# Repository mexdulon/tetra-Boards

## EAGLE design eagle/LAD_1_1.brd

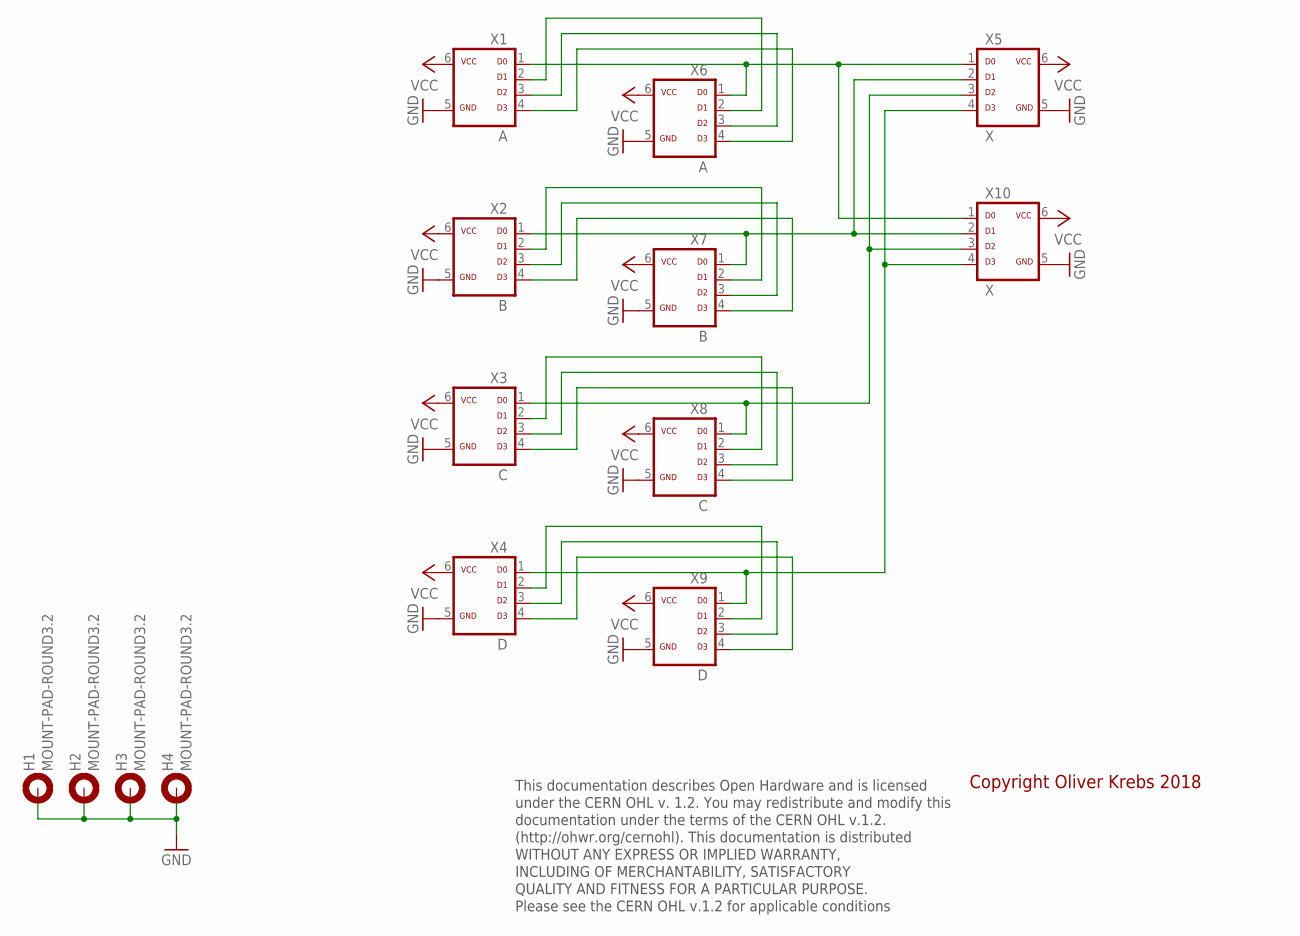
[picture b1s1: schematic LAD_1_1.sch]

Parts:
H1, H2, H3, H4: MOUNT-PAD-ROUND3.2; 3,2-PAD
X1, X6: A; ML-6
X2, X7: B; ML-6
X3, X8: C; ML-6
X4, X9: D; ML-6
X5, X10: X; ML-6

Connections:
GND: H1.B3,2, H2.B3,2, H3.B3,2, H4.B3,2, X1.5, X2.5, X3.5, X4.5, X5.5, X6.5, X7.5, X8.5, X9.5, X10.5
unnamed: X1.2, X6.2
unnamed: X1.3, X6.3
unnamed: X1.4, X6.4
unnamed: X4.1, X5.4, X9.1, X10.4
unnamed: X2.4, X7.4
unnamed: X3.1, X5.3, X8.1, X10.3
unnamed: X2.1, X5.2, X7.1, X10.2
unnamed: X1.1, X5.1, X6.1, X10.1
unnamed: X2.3, X7.3
unnamed: X2.2, X7.2
unnamed: X3.2, X8.2
unnamed: X3.3, X8.3
unnamed: X3.4, X8.4
unnamed: X4.2, X9.2
unnamed: X4.3, X9.3
unnamed: X4.4, X9.4
VCC: X1.6, X2.6, X3.6, X4.6, X5.6, X6.6, X7.6, X8.6, X9.6, X10.6

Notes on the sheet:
This documentation describes Open Hardware and is licensed under the CERN OHL v. 1.2. You may redistribute and modify this documentation under the terms of the CERN OHL v.1.2. (http://ohwr.org/cernohl). This documentation is distributed WITHOUT ANY EXPRESS OR IMPLIED WARRANTY, INCLUDING OF MERCHANT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
Copyright Oliver Krebs 2018

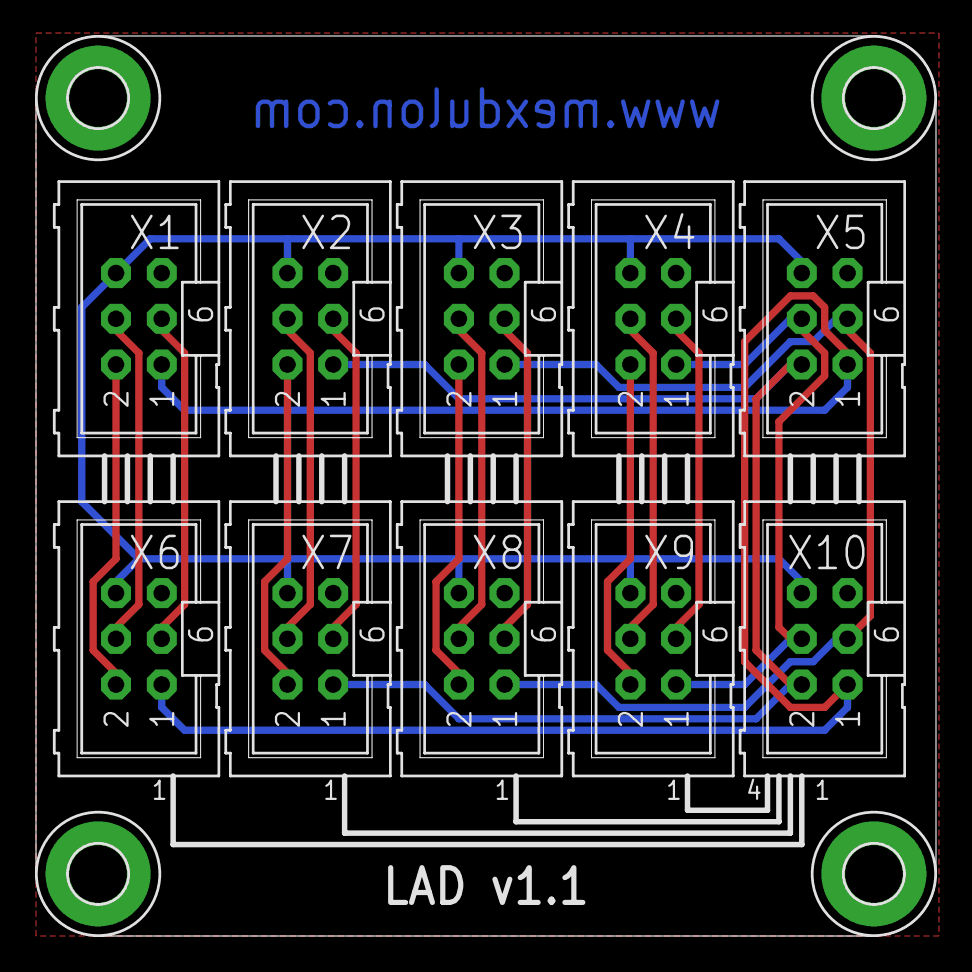
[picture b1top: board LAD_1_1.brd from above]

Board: 2 copper layers, 50.0 x 50.0 mm, 14 parts (0 on the bottom side), 18 nets.

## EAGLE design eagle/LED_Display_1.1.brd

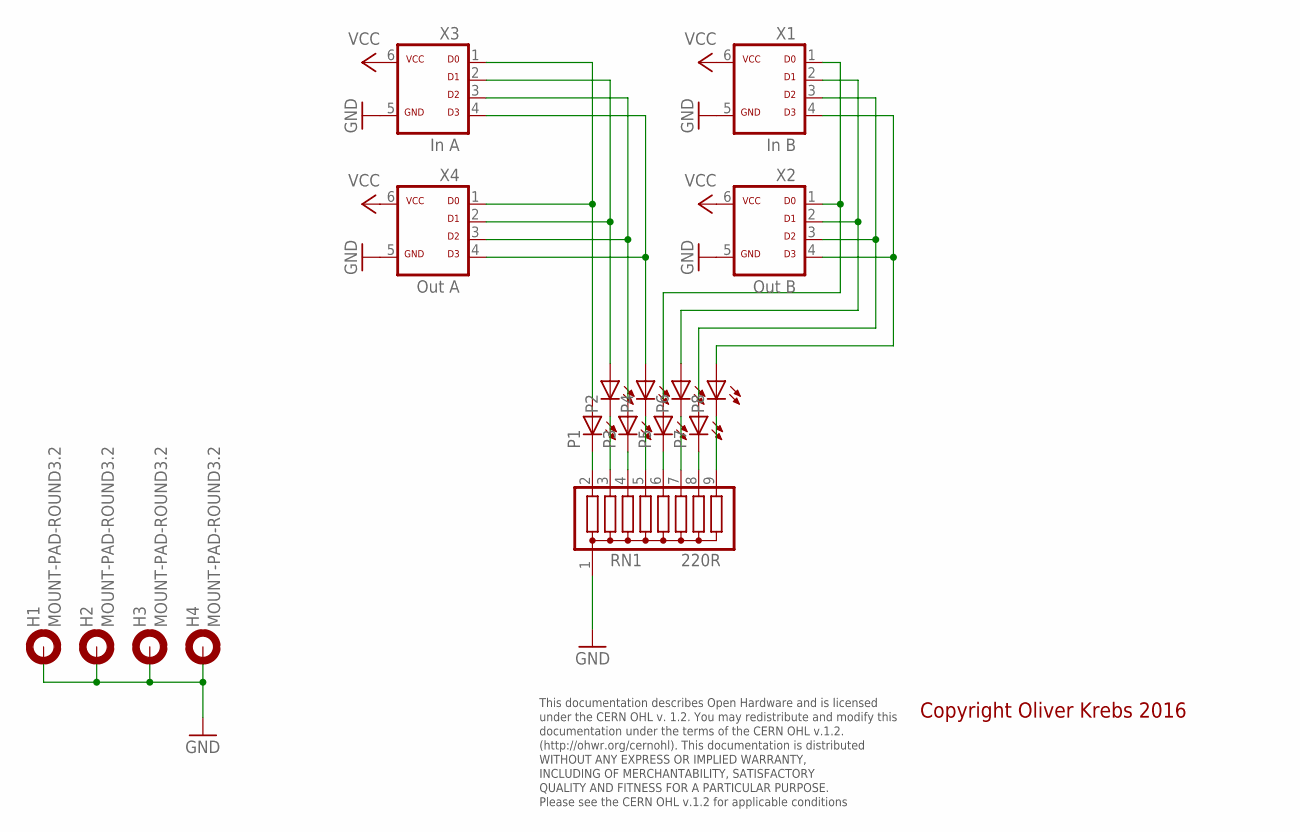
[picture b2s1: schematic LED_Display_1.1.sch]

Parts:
H1, H2, H3, H4: MOUNT-PAD-ROUND3.2; 3,2-PAD
P1, P2, P3, P4, P5, P6, P7, P8: LED3MM
RN1: 220R; SIL9
X1: In B; ML-6
X2: Out B; ML-6
X3: In A; ML-6
X4: Out A; ML-6

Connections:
GND: H1.B3,2, H2.B3,2, H3.B3,2, H4.B3,2, RN1.1, X1.5, X2.5, X3.5, X4.5
unnamed: P5.A, X1.1, X2.1
unnamed: P6.A, X1.2, X2.2
unnamed: P1.A, X3.1, X4.1
unnamed: P8.A, X1.4, X2.4
unnamed: P5.K (C), RN1.6
unnamed: P7.A, X1.3, X2.3
unnamed: P2.A, X3.2, X4.2
unnamed: P4.A, X3.4, X4.4
unnamed: P3.A, X3.3, X4.3
unnamed: P6.K (C), RN1.7
unnamed: P7.K (C), RN1.8
unnamed: P4.K (C), RN1.5
unnamed: P3.K (C), RN1.4
unnamed: P2.K (C), RN1.3
unnamed: P1.K (C), RN1.2
P6: P8.K (C), RN1.9
VCC: X1.6, X2.6, X3.6, X4.6

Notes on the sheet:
This documentation describes Open Hardware and is licensed under the CERN OHL v. 1.2. You may redistribute and modify this documentation under the terms of the CERN OHL v.1.2. (http://ohwr.org/cernohl). This documentation is distributed WITHOUT ANY EXPRESS OR IMPLIED WARRANTY, INCLUDING OF MERCHANT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
Copyright Oliver Krebs 2016

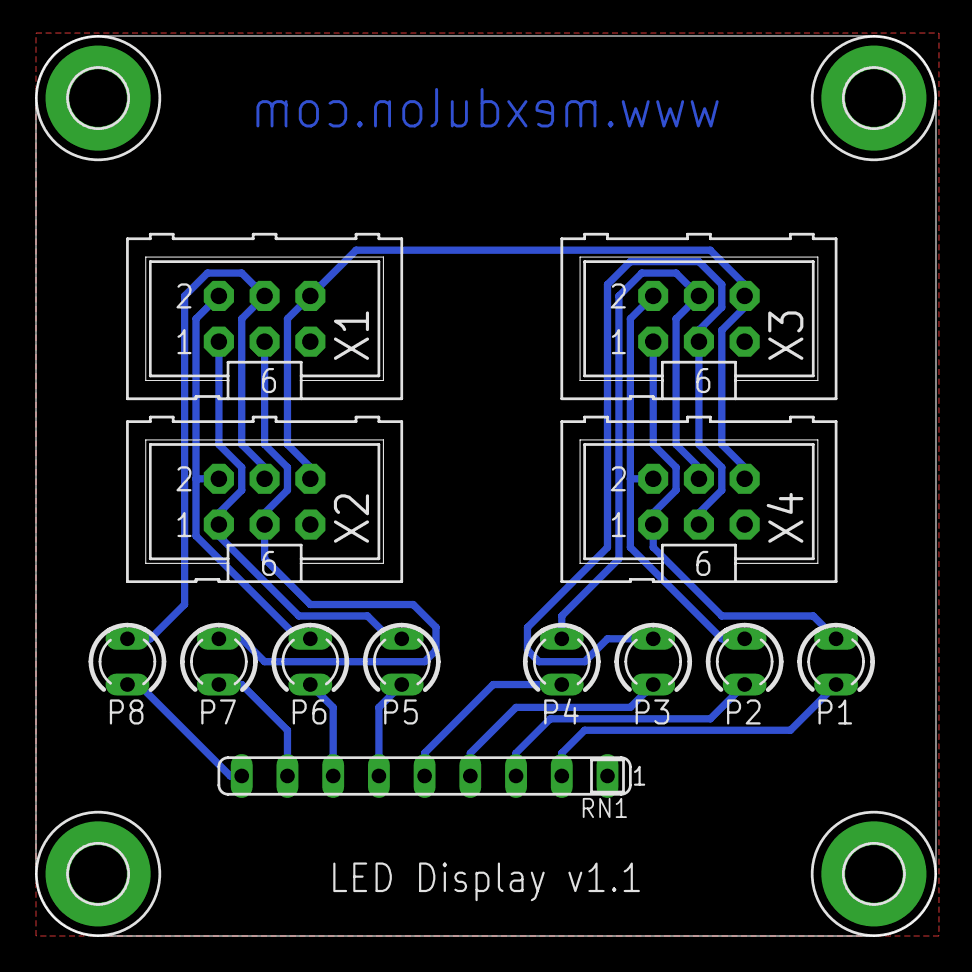
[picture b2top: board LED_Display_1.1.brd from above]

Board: 2 copper layers, 50.0 x 50.0 mm, 17 parts (0 on the bottom side), 18 nets.

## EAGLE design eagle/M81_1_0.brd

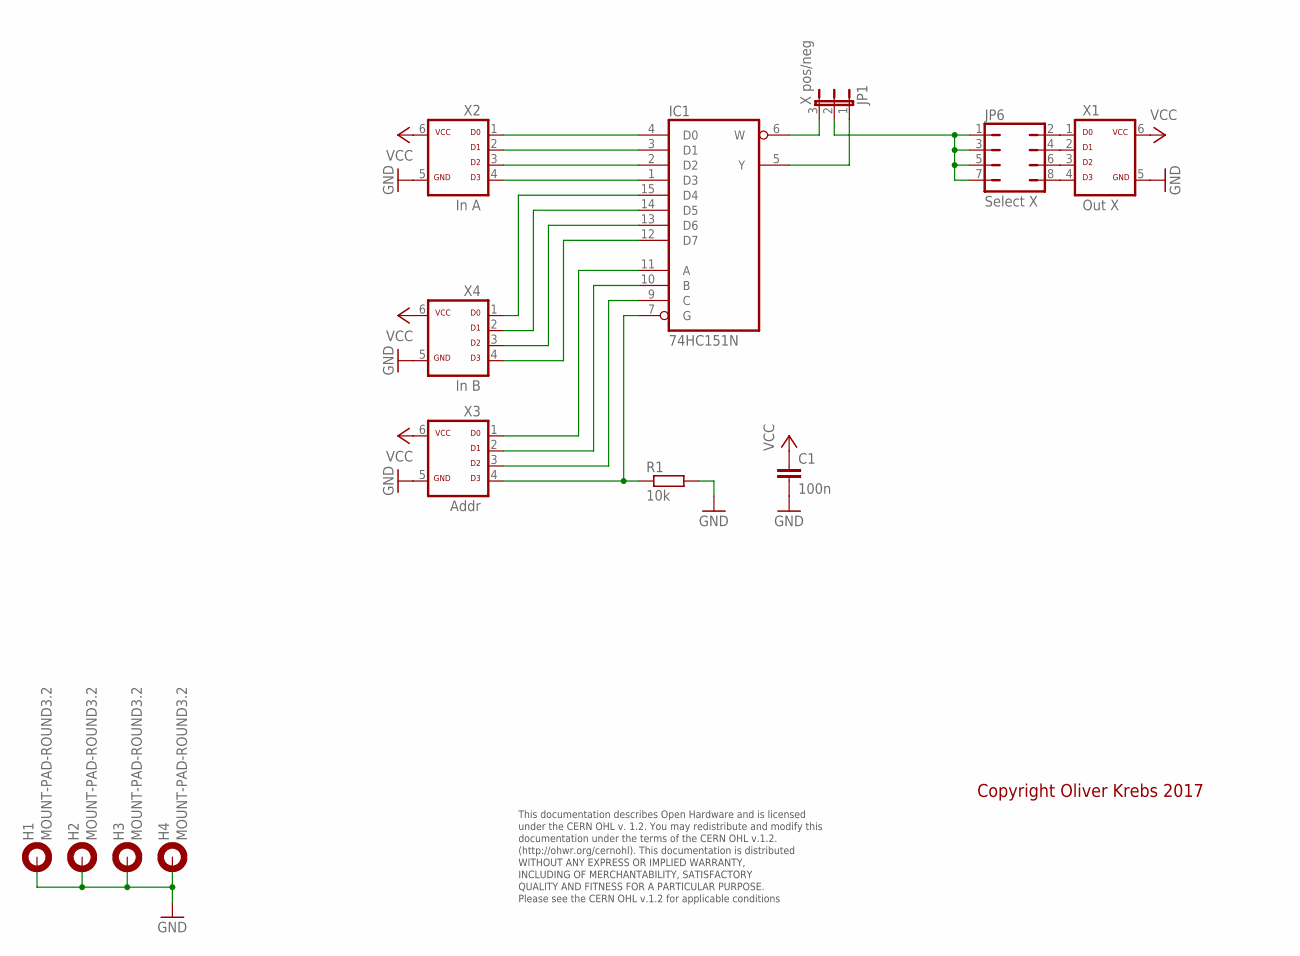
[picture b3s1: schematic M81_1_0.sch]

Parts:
C1: 100n; C050-025X075
H1, H2, H3, H4: MOUNT-PAD-ROUND3.2; 3,2-PAD
IC1: 74HC151N; DIL16
JP1: X pos/neg; JP2
JP6: Select X; JP4Q
R1: 10k; 0207/10
X1: Out X; ML-6
X2: In A; ML-6
X3: Addr; ML-6
X4: In B; ML-6

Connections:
GND: C1.2, H1.B3,2, H2.B3,2, H3.B3,2, H4.B3,2, IC1.8 (GND), R1.2, X1.5, X2.5, X3.5, X4.5
unnamed: IC1.5 (Y), JP1.1
unnamed: IC1.6 (W), JP1.3
unnamed: JP1.2, JP6.1, JP6.3, JP6.5, JP6.7
unnamed: IC1.4 (D0), X2.1
unnamed: IC1.3 (D1), X2.2
unnamed: IC1.2 (D2), X2.3
unnamed: IC1.1 (D3), X2.4
unnamed: IC1.15 (D4), X4.1
unnamed: IC1.14 (D5), X4.2
unnamed: IC1.13 (D6), X4.3
unnamed: IC1.12 (D7), X4.4
unnamed: IC1.11 (A), X3.1
unnamed: IC1.10 (B), X3.2
unnamed: IC1.9 (C), X3.3
unnamed: IC1.7 (G), R1.1, X3.4
unnamed: JP6.2, X1.1
unnamed: JP6.4, X1.2
unnamed: JP6.6, X1.3
unnamed: JP6.8, X1.4
VCC: C1.1, IC1.16 (VCC), X1.6, X2.6, X3.6, X4.6

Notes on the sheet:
This documentation describes Open Hardware and is licensed under the CERN OHL v. 1.2. You may redistribute and modify this documentation under the terms of the CERN OHL v.1.2. (http://ohwr.org/cernohl). This documentation is distributed WITHOUT ANY EXPRESS OR IMPLIED WARRANTY, INCLUDING OF MERCHANT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
Copyright Oliver Krebs 2017

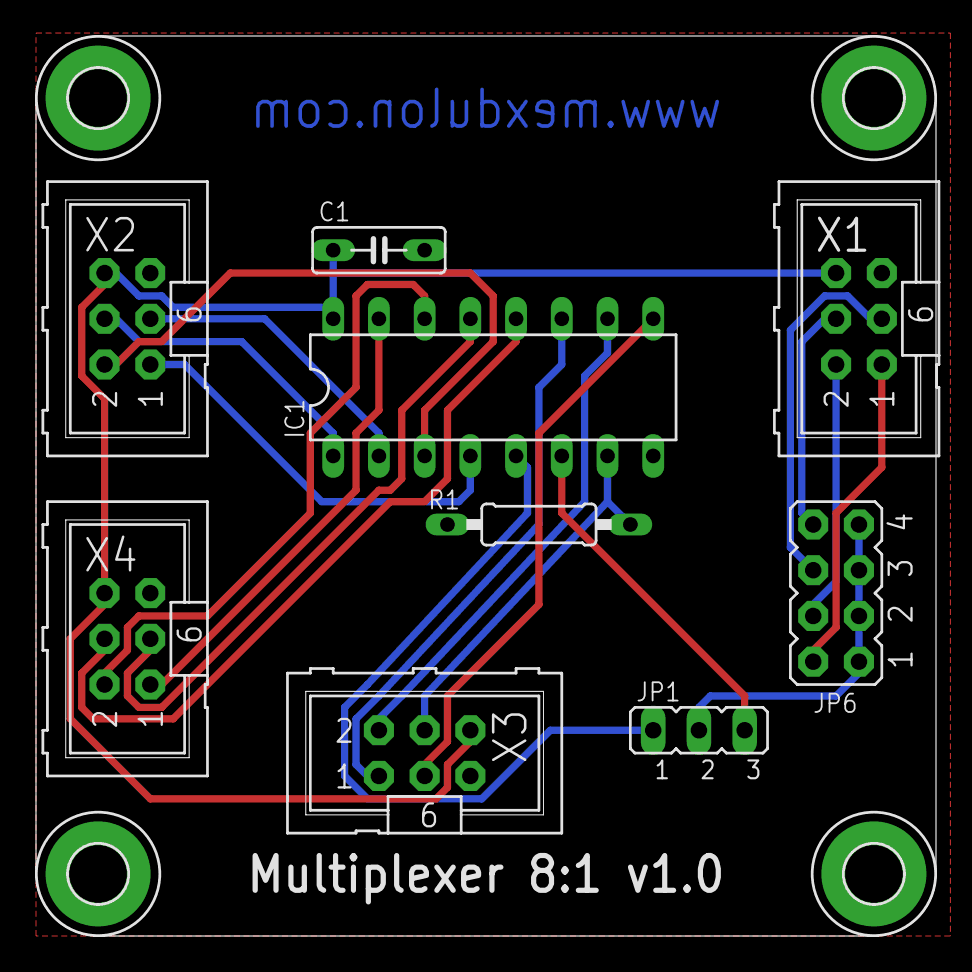
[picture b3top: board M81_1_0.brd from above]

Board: 2 copper layers, 50.0 x 50.0 mm, 13 parts (0 on the bottom side), 21 nets.

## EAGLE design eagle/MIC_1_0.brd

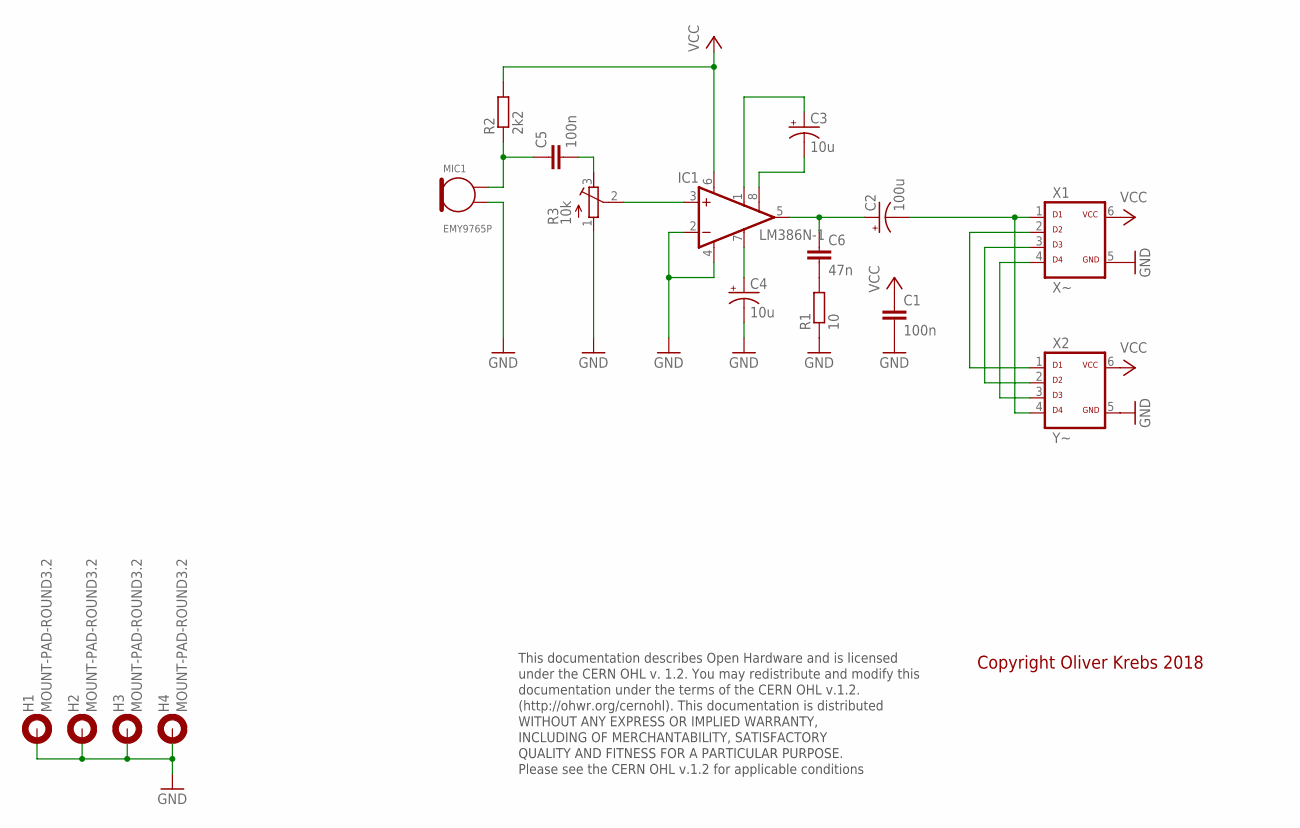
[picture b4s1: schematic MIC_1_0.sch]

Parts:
C1, C5: 100n; C050-025X075
C2: 100u; CPOL-RADIAL-100UF-25V
C3, C4: 10u; CPOL-RADIAL-10UF-25V
C6: 47n; C050-025X075
H1, H2, H3, H4: MOUNT-PAD-ROUND3.2; 3,2-PAD
IC1: LM386N-1; DIL08
MIC1: EMY9765P
R1: 10; 0207/10
R2: 2k2; 0207/10
R3: 10k; ACP-6L
X1: X~; ML-6
X2: Y~; ML-6

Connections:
GND: C1.2, C4.2 (-), H1.B3,2, H2.B3,2, H3.B3,2, H4.B3,2, IC1.2 (-IN), IC1.4 (GND), MIC1.P$2, R1.1, R3.1 (A), X1.5, X2.5
unnamed: C3.2 (-), IC1.8 (GAIN)
unnamed: C3.1 (+), IC1.1 (GAIN)
unnamed: C5.2, R3.3 (E)
unnamed: X1.4, X2.3
unnamed: C5.1, MIC1.P$1, R2.1
unnamed: IC1.3 (+IN), R3.2 (S)
unnamed: X1.3, X2.2
unnamed: C4.1 (+), IC1.7 (BYPASS)
unnamed: C2.1 (+), C6.1, IC1.5 (OUT)
unnamed: C6.2, R1.2
unnamed: C2.2 (-), X1.1, X2.4
unnamed: X1.2, X2.1
VCC: C1.1, IC1.6 (VS), R2.2, X1.6, X2.6

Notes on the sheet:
This documentation describes Open Hardware and is licensed under the CERN OHL v. 1.2. You may redistribute and modify this documentation under the terms of the CERN OHL v.1.2. (http://ohwr.org/cernohl). This documentation is distributed WITHOUT ANY EXPRESS OR IMPLIED WARRANTY, INCLUDING OF MERCHANT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
Copyright Oliver Krebs 2018

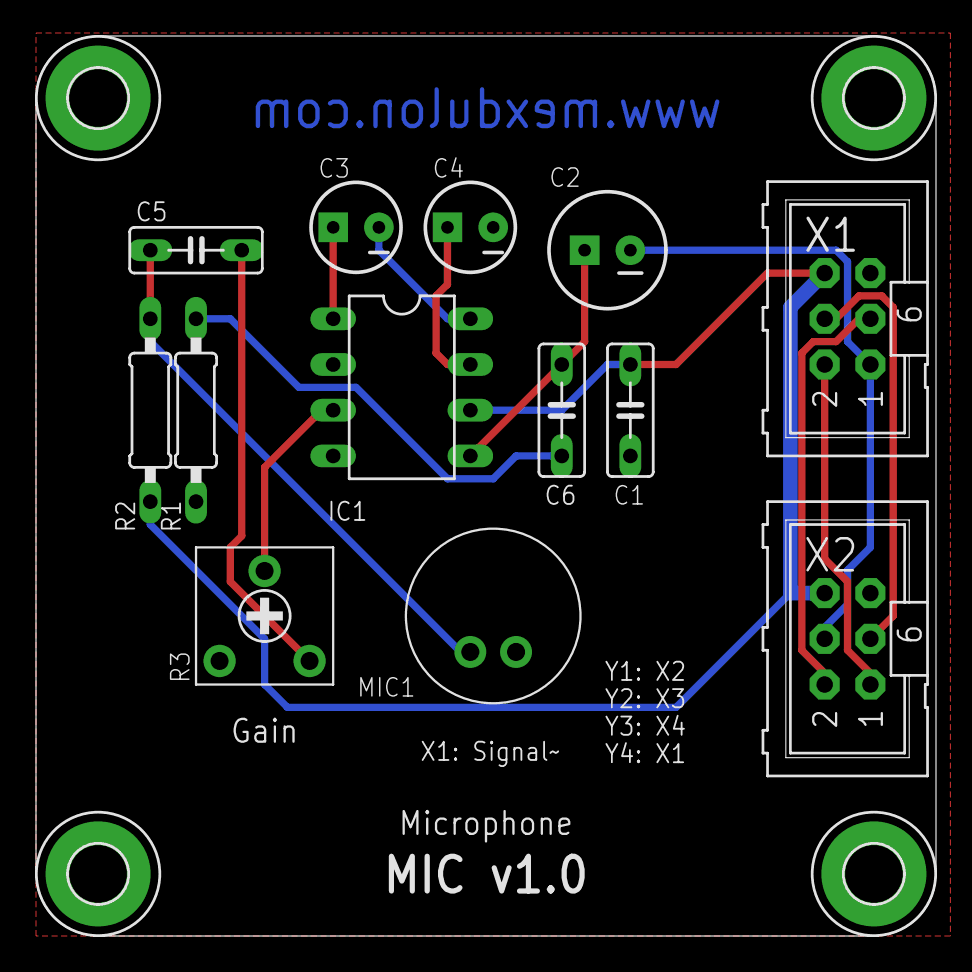
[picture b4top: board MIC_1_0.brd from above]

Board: 2 copper layers, 50.0 x 50.0 mm, 17 parts (0 on the bottom side), 14 nets.

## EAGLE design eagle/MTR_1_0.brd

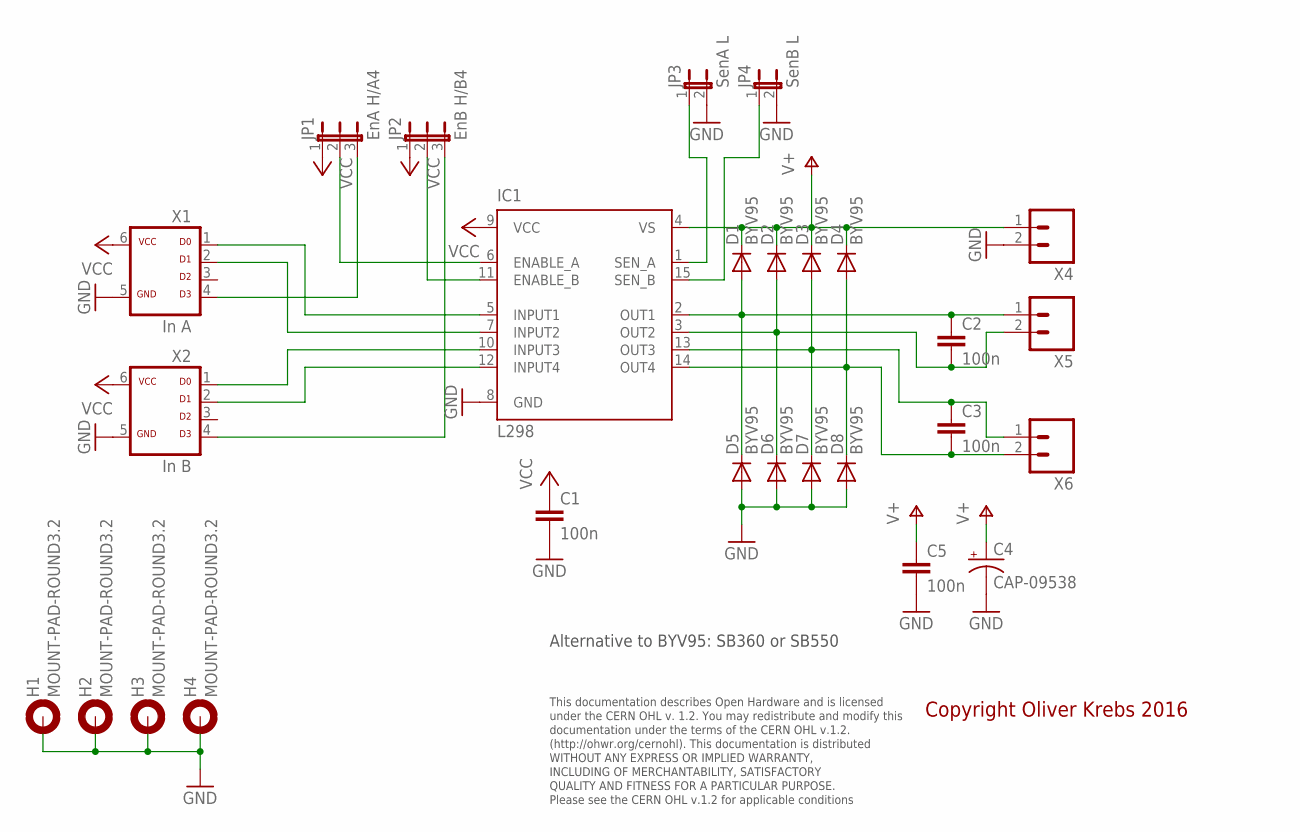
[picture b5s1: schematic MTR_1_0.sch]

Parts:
C1, C2, C3, C5: 100n; C050-025X075
C4: CAP-09538; CPOL-RADIAL-1000UF-25V
D1, D2, D3, D4, D5, D6, D7, D8: BYV95; SOD57-10
H1, H2, H3, H4: MOUNT-PAD-ROUND3.2; 3,2-PAD
IC1: L298; MULTIWATT-15
JP1: EnA H/A4; JP2-U
JP2: EnB H/B4; JP2-U
JP3: SenA L; JP1
JP4: SenB L; JP1
X1: In A; ML-6
X2: In B; ML-6
X4, X5, X6: M021.3MM-5.08; 1X02_BIG_5.08

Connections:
GND: C1.2, C4.-, C5.2, D5.A, D6.A, D7.A, D8.A, H1.B3,2, H2.B3,2, H3.B3,2, H4.B3,2, IC1.8 (GND), JP3.2, JP4.2, X1.5, X2.5, X4.2
unnamed: JP2.3, X2.4
unnamed: IC1.6 (ENABLE_A), JP1.2
unnamed: IC1.11 (ENABLE_B), JP2.2
unnamed: JP1.3, X1.4
unnamed: C2.1, D1.A, D5.C, IC1.2 (OUT1), X5.1
unnamed: C2.2, D2.A, D6.C, IC1.3 (OUT2), X5.2
unnamed: C3.1, D3.A, D7.C, IC1.13 (OUT3), X6.1
unnamed: C3.2, D4.A, D8.C, IC1.14 (OUT4), X6.2
unnamed: IC1.5 (INPUT1), X1.1
unnamed: IC1.1 (SEN_A), JP3.1
unnamed: IC1.15 (SEN_B), JP4.1
unnamed: IC1.7 (INPUT2), X1.2
unnamed: IC1.10 (INPUT3), X2.1
unnamed: IC1.12 (INPUT4), X2.2
V+: C4.+, C5.1, D1.C, D2.C, D3.C, D4.C, IC1.4 (VS), X4.1
VCC: C1.1, IC1.9 (VCC), JP1.1, JP2.1, X1.6, X2.6

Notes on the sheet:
This documentation describes Open Hardware and is licensed under the CERN OHL v. 1.2. You may redistribute and modify this documentation under the terms of the CERN OHL v.1.2. (http://ohwr.org/cernohl). This documentation is distributed WITHOUT ANY EXPRESS OR IMPLIED WARRANTY, INCLUDING OF MERCHANT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
Copyright Oliver Krebs 2016
Alternative to BYV95: SB360 or SB550

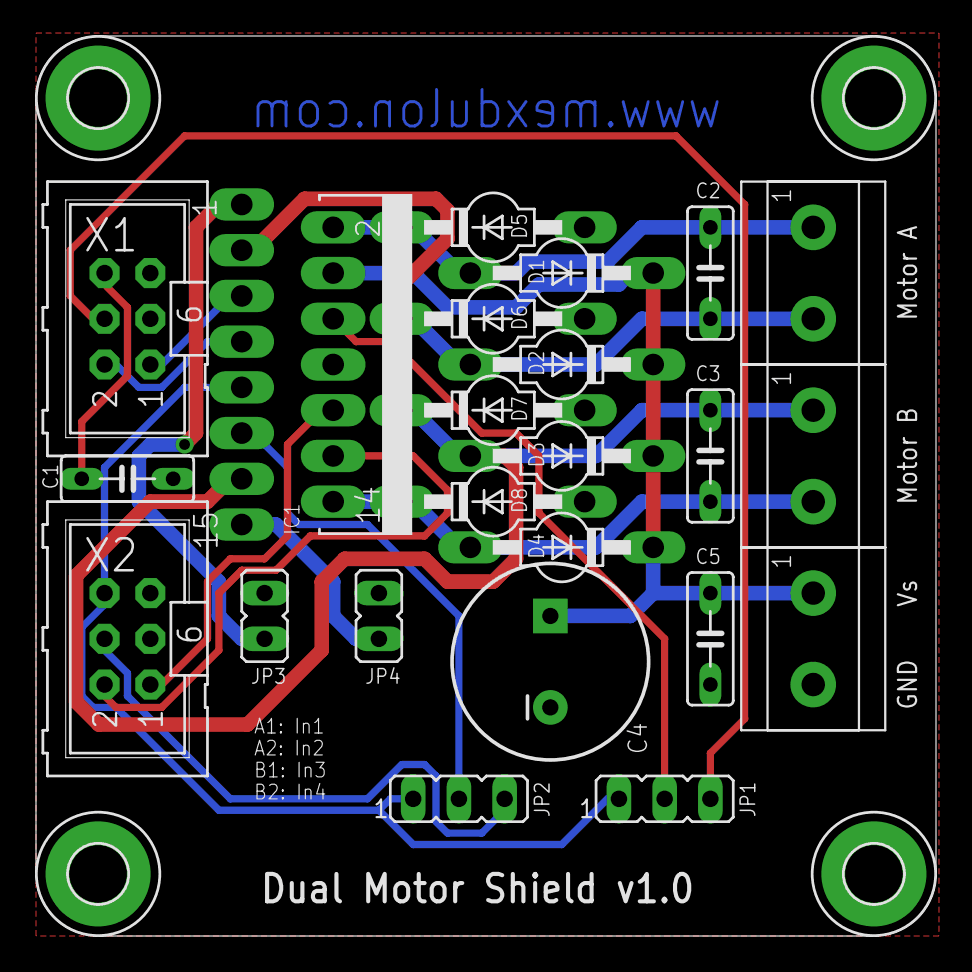
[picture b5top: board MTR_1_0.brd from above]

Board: 2 copper layers, 50.0 x 50.0 mm, 27 parts (0 on the bottom side), 17 nets.

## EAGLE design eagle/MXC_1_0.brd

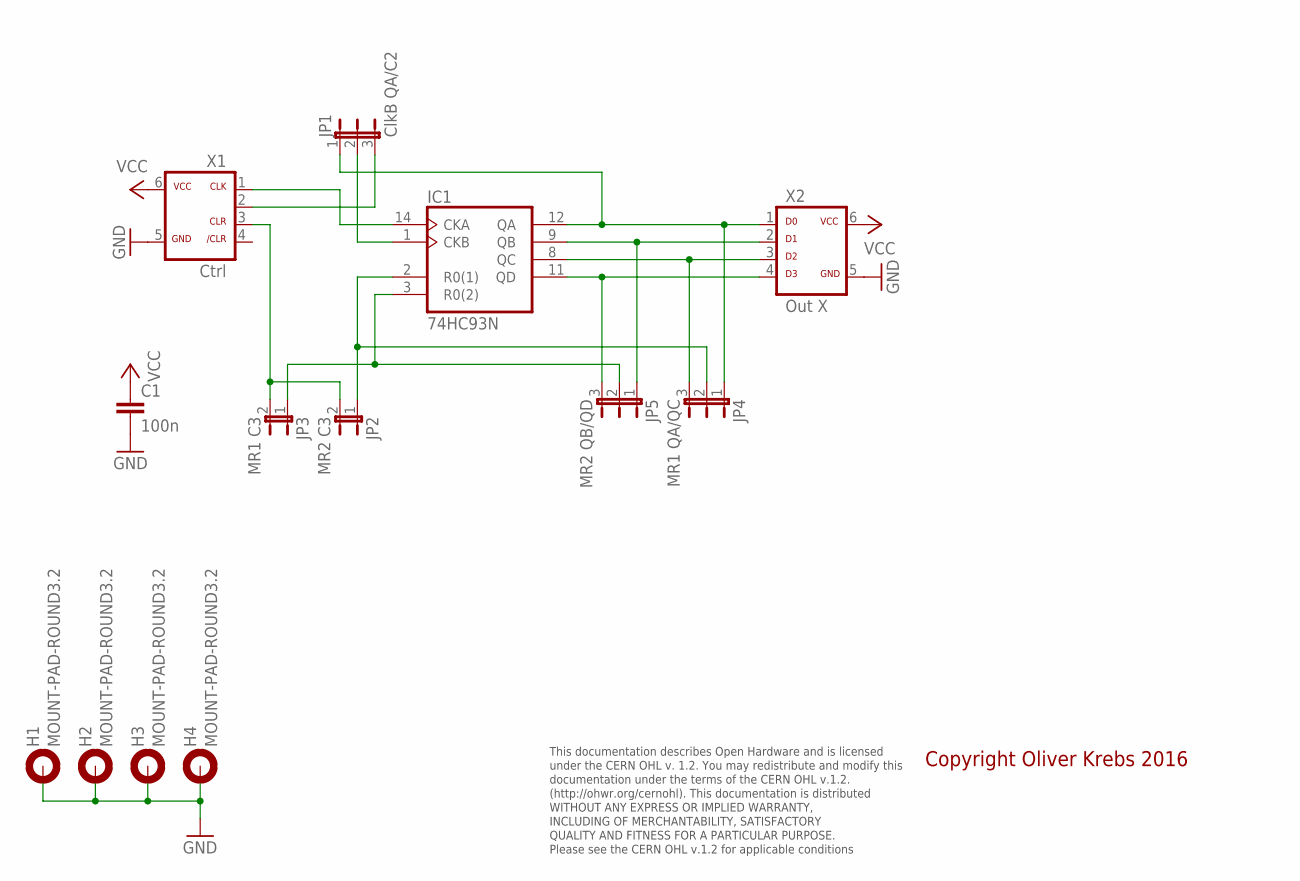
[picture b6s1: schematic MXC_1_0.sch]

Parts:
C1: 100n; C050-025X075
H1, H2, H3, H4: MOUNT-PAD-ROUND3.2; 3,2-PAD
IC1: 74HC93N; DIL14
JP1: ClkB QA/C2; JP2-U
JP2: MR2 C3; JP1
JP3: MR1 C3; JP1
JP4: MR1 QA/QC; JP2-U
JP5: MR2 QB/QD; JP2-U
X1: Ctrl; ML-6
X2: Out X; ML-6

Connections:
GND: C1.2, H1.B3,2, H2.B3,2, H3.B3,2, H4.B3,2, IC1.10 (GND), X1.5, X2.5
unnamed: IC1.14 (CKA), X1.1
unnamed: IC1.1 (CKB), JP1.2
unnamed: IC1.12 (QA), JP1.1, JP4.1, X2.1
unnamed: IC1.2 (R0(1)), JP2.1, JP4.2
unnamed: IC1.9 (QB), JP5.1, X2.2
unnamed: IC1.8 (QC), JP4.3, X2.3
unnamed: IC1.11 (QD), JP5.3, X2.4
unnamed: IC1.3 (R0(2)), JP3.1, JP5.2
unnamed: JP1.3, X1.2
unnamed: JP2.2, JP3.2, X1.3
VCC: C1.1, IC1.5 (VCC), X1.6, X2.6

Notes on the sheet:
This documentation describes Open Hardware and is licensed under the CERN OHL v. 1.2. You may redistribute and modify this documentation under the terms of the CERN OHL v.1.2. (http://ohwr.org/cernohl). This documentation is distributed WITHOUT ANY EXPRESS OR IMPLIED WARRANTY, INCLUDING OF MERCHANT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
Copyright Oliver Krebs 2016

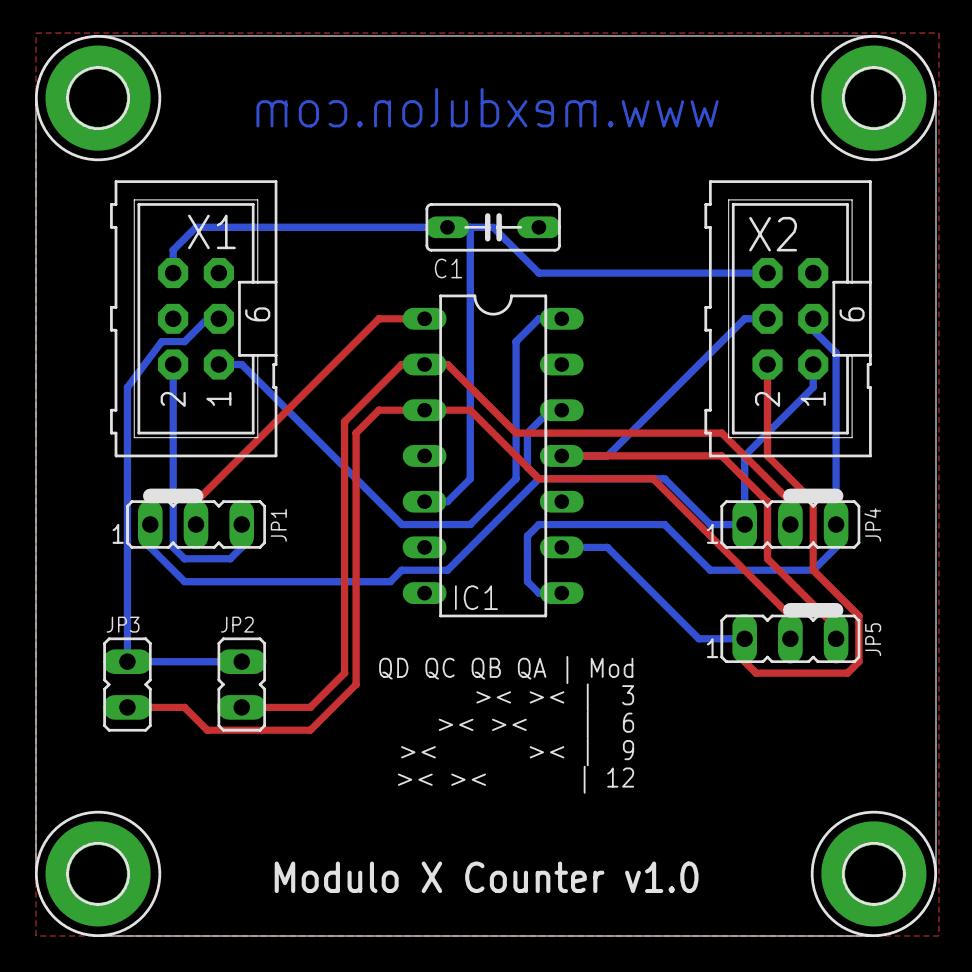
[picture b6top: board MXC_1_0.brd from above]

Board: 2 copper layers, 50.0 x 50.0 mm, 13 parts (0 on the bottom side), 12 nets.

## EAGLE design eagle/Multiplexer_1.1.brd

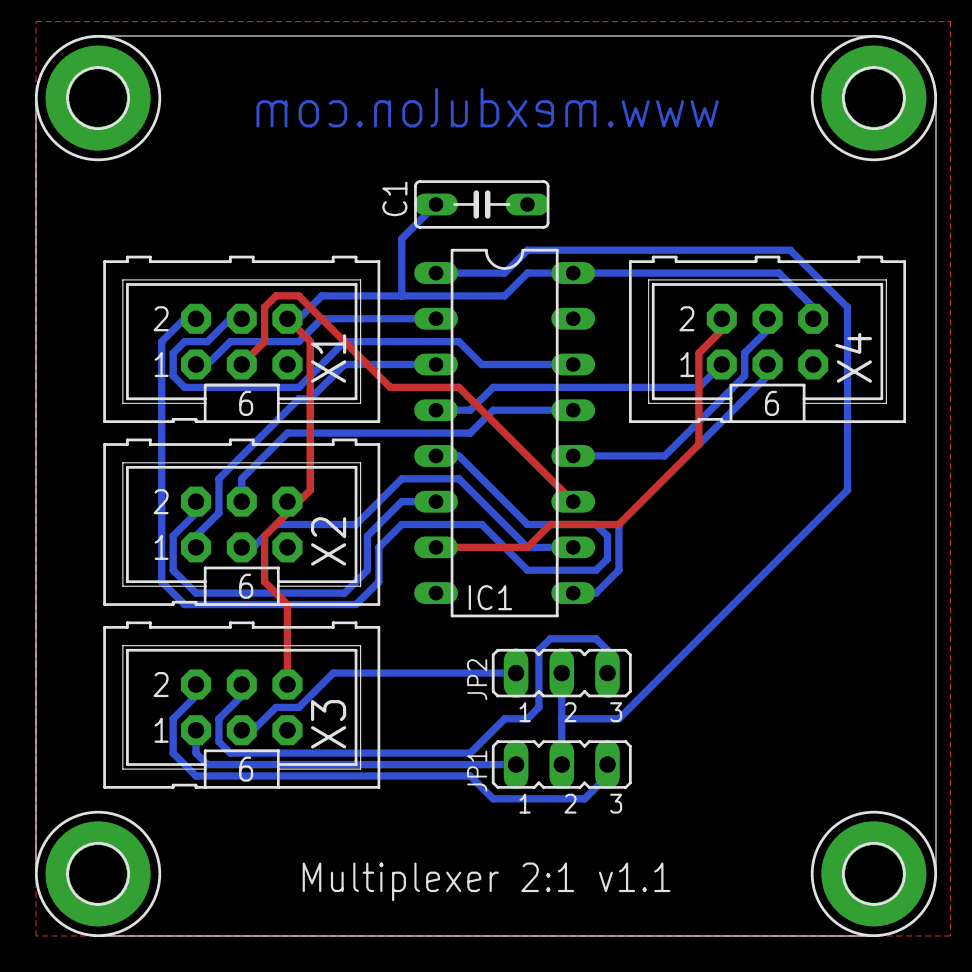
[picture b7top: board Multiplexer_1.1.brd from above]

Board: 2 copper layers, 50.0 x 50.0 mm, 12 parts (0 on the bottom side), 19 nets.

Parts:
C1: 100n; C050-025X075
H1, H2, H3, H4: MOUNT-PAD-ROUND3.2; 3,2-PAD
IC1: 74HC157N; DIL16
JP1: S 1/2; JP2
JP2: S 3/4; JP2
X1: In A; ML-6
X2: In B; ML-6
X3: Select; ML-6
X4: Out; ML-6

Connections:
GND: C1.2, H1.B3,2, H2.B3,2, H3.B3,2, H4.B3,2, IC1.8, IC1.15, X1.5, X2.5, X3.5, X4.5
unnamed: IC1.2, X1.1
unnamed: IC1.5, X1.2
unnamed: IC1.11, X1.3
unnamed: IC1.14, X1.4
unnamed: IC1.3, X2.1
unnamed: IC1.6, X2.2
unnamed: IC1.10, X2.3
unnamed: IC1.13, X2.4
unnamed: IC1.4, X4.1
unnamed: IC1.7, X4.2
unnamed: IC1.9, X4.3
unnamed: IC1.12, X4.4
unnamed: IC1.1, JP1.2, JP2.2
unnamed: JP1.3, X3.2
unnamed: JP2.1, X3.3
unnamed: JP1.1, X3.1
unnamed: JP2.3, X3.4
VCC: C1.1, IC1.16, X1.6, X2.6, X3.6, X4.6

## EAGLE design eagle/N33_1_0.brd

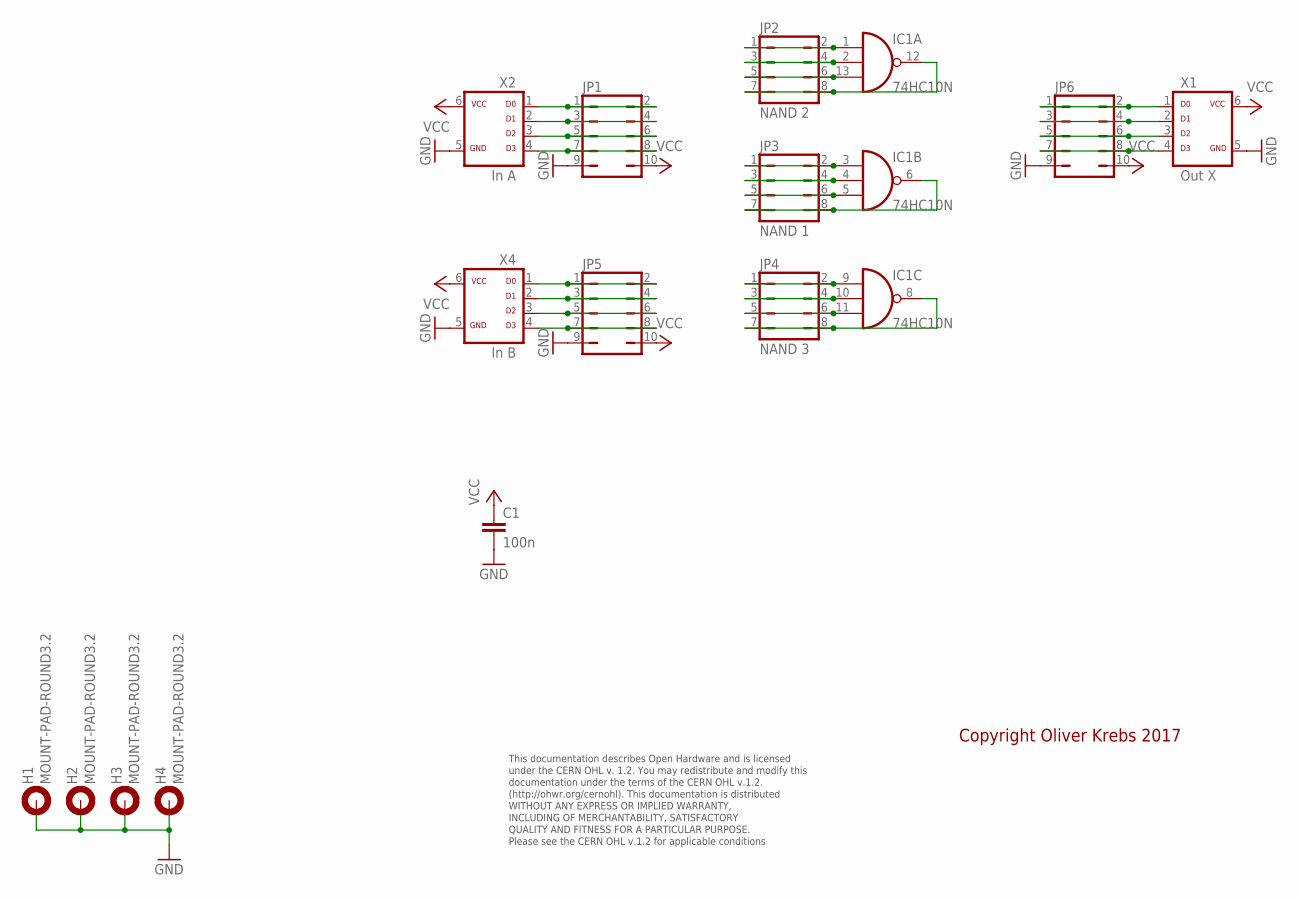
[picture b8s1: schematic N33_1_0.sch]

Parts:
C1: 100n; C050-025X075
H1, H2, H3, H4: MOUNT-PAD-ROUND3.2; 3,2-PAD
IC1: 74HC10N; DIL14
JP1, JP5, JP6: JP5Q
JP2: NAND 2; JP4Q
JP3: NAND 1; JP4Q
JP4: NAND 3; JP4Q
X1: Out X; ML-6
X2: In A; ML-6
X4: In B; ML-6

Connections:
GND: C1.2, H1.B3,2, H2.B3,2, H3.B3,2, H4.B3,2, IC1.7 (GND), JP1.9, JP5.9, JP6.9, X1.5, X2.5, X4.5
unnamed: IC1.1 (I0), JP2.1, JP2.2
unnamed: IC1.2 (I1), JP2.3, JP2.4
unnamed: IC1.13 (I2), JP2.5, JP2.6
unnamed: IC1.3 (I0), JP3.1, JP3.2
unnamed: IC1.4 (I1), JP3.3, JP3.4
unnamed: JP5.1, JP5.2, X4.1
unnamed: JP5.3, JP5.4, X4.2
unnamed: JP5.5, JP5.6, X4.3
unnamed: JP5.7, JP5.8, X4.4
unnamed: IC1.5 (I2), JP3.5, JP3.6
unnamed: IC1.9 (I0), JP4.1, JP4.2
unnamed: IC1.10 (I1), JP4.3, JP4.4
unnamed: IC1.11 (I2), JP4.5, JP4.6
unnamed: JP1.1, JP1.2, X2.1
unnamed: JP1.3, JP1.4, X2.2
unnamed: JP1.5, JP1.6, X2.3
unnamed: JP1.7, JP1.8, X2.4
unnamed: JP6.1, JP6.2, X1.1
unnamed: JP6.3, JP6.4, X1.2
unnamed: JP6.5, JP6.6, X1.3
unnamed: JP6.7, JP6.8, X1.4
unnamed: IC1.8 (O), JP4.7, JP4.8
unnamed: IC1.6 (O), JP3.7, JP3.8
unnamed: IC1.12 (O), JP2.7, JP2.8
VCC: C1.1, IC1.14 (VCC), JP1.10, JP5.10, JP6.10, X1.6, X2.6, X4.6

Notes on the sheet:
This documentation describes Open Hardware and is licensed under the CERN OHL v. 1.2. You may redistribute and modify this documentation under the terms of the CERN OHL v.1.2. (http://ohwr.org/cernohl). This documentation is distributed WITHOUT ANY EXPRESS OR IMPLIED WARRANTY, INCLUDING OF MERCHANT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
Copyright Oliver Krebs 2017

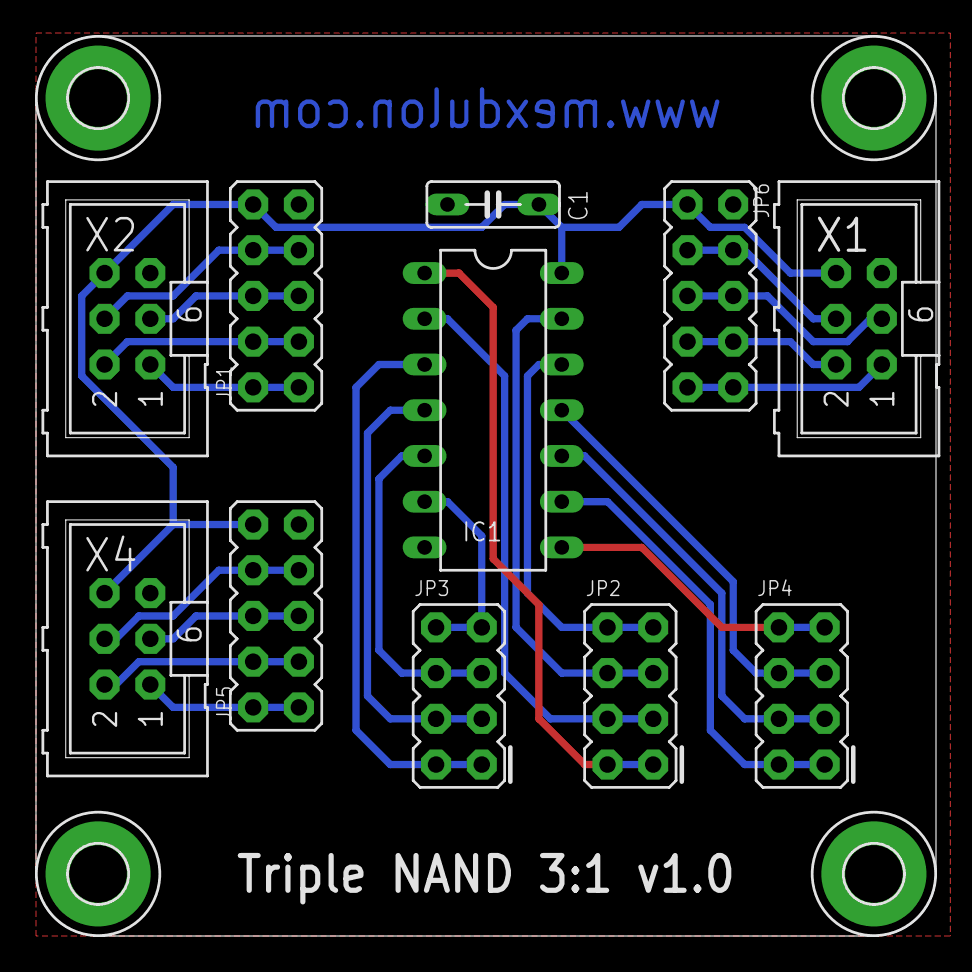
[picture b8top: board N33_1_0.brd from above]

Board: 2 copper layers, 50.0 x 50.0 mm, 15 parts (0 on the bottom side), 26 nets.

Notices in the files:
eagle/LAD_1_1.brd:
Licensed under CERN OHL v.1.2
parts and their libraries:
SparkFun-Passives: Licensing: Creative Commons ShareAlike 4.0 International - https://creativecommons.org/licenses/by-sa/4.0
